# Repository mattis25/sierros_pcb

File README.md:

# sierros_pcb
Circuit of Sierros Project (self-service device which does a resuscitation) OPEN HARDWARE

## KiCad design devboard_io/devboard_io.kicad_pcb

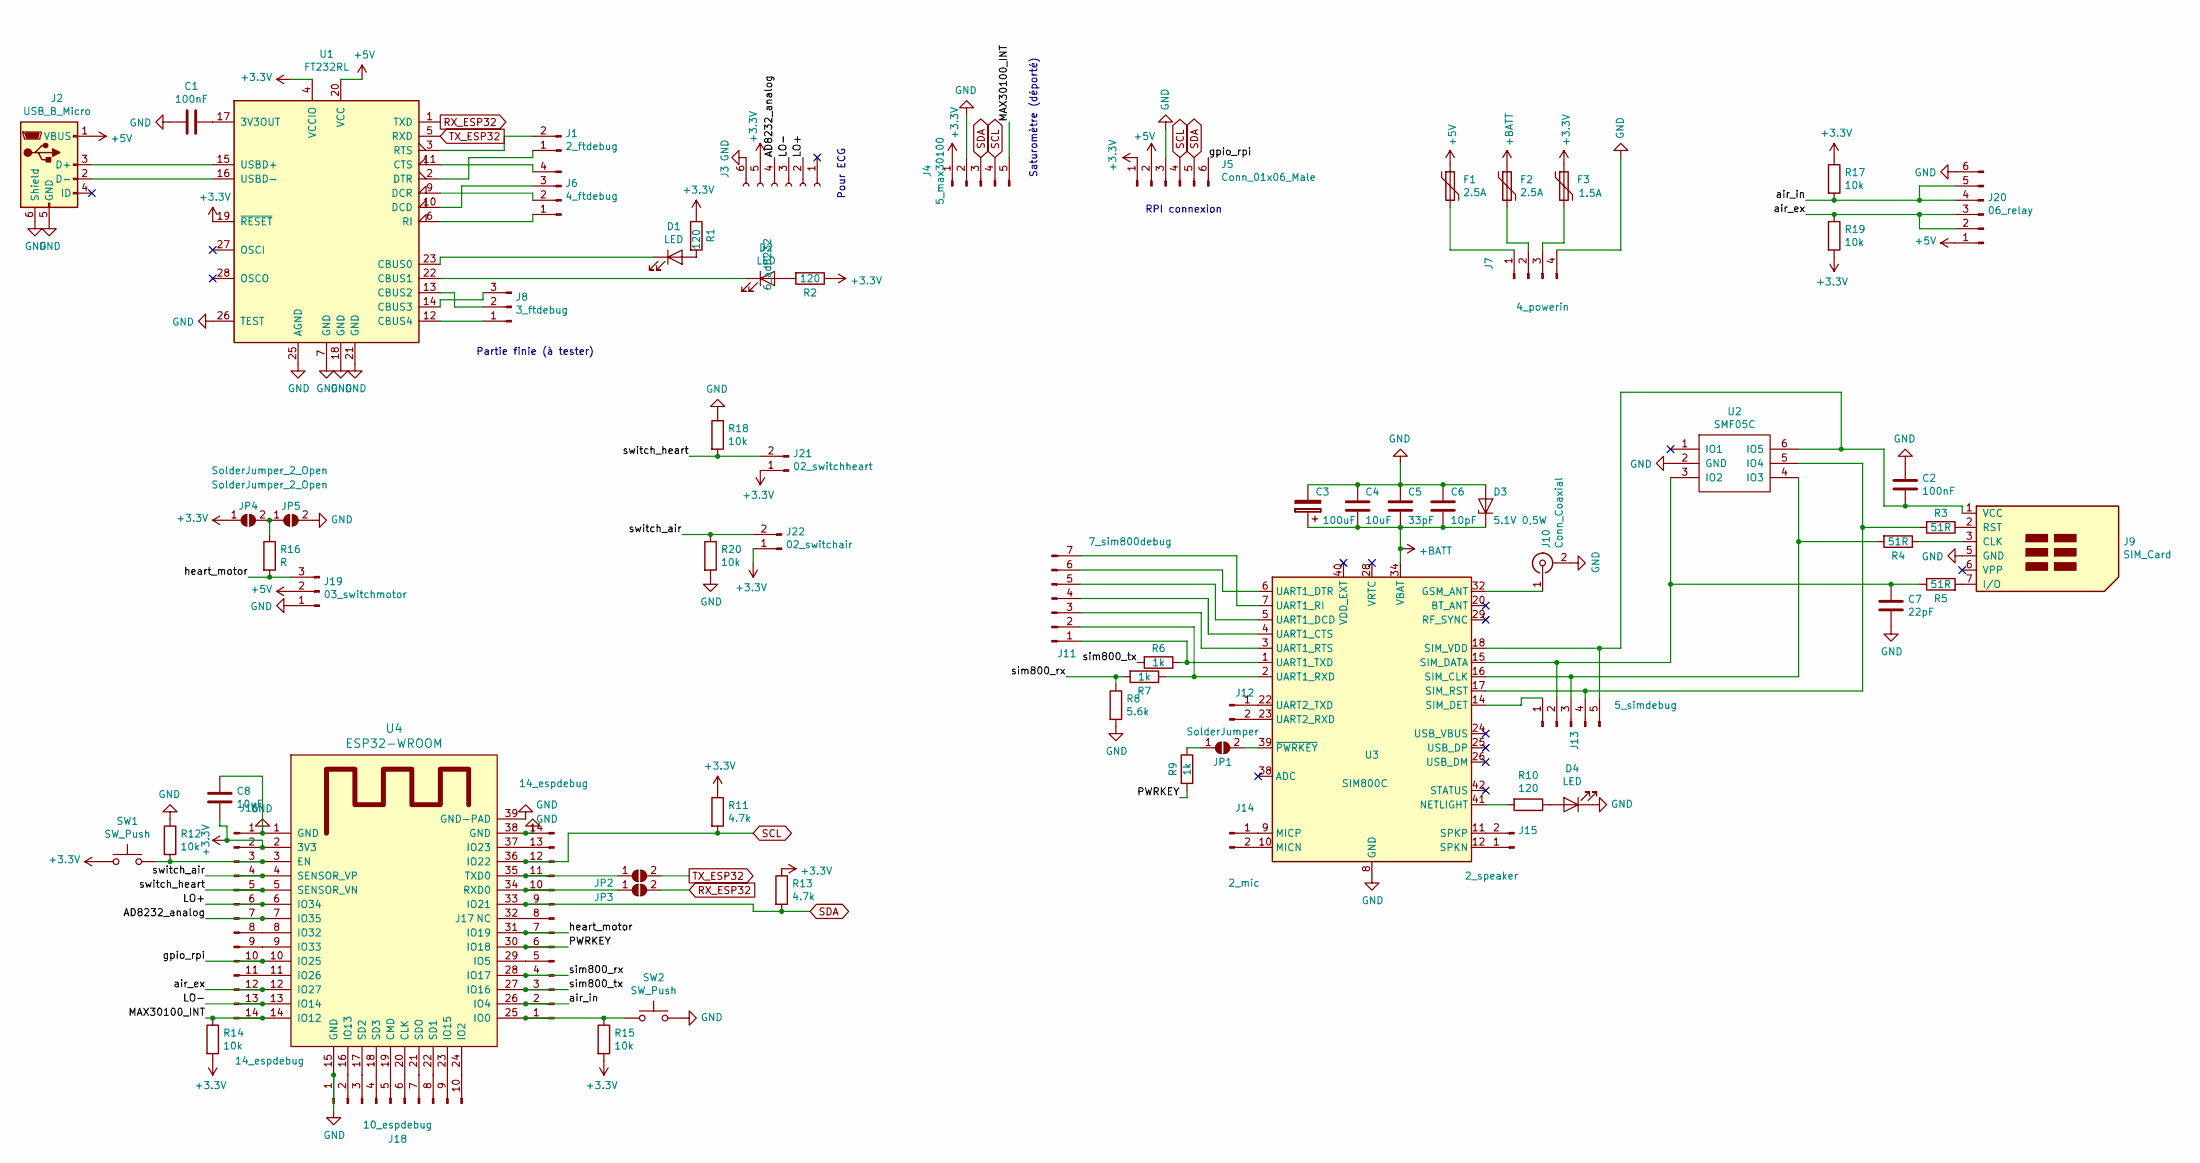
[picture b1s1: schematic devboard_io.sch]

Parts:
C1, C2: 100nF; C_1206_HandSoldering
C3: 100uF; CP_Tantalum_Case-D_EIA-7343-31_Hand
C4, C8: 10uF; C_1210_HandSoldering
C5: 33pF; C_0603_HandSoldering
C6: 10pF; C_0805_HandSoldering
C7: 22pF; C_1206_HandSoldering
D1, D2, D4: LED; LED_0805_HandSoldering
D3: 5.1V 0,5W; D_1206
F1, F2: 2.5A; C_1812_HandSoldering
F3: 1.5A; C_1812_HandSoldering
J1: 2_ftdebug; Pin_Header_Straight_1x02_Pitch2.54mm
J2: USB_B_Micro; USB-MICRO-B
J3: 6_ad8232; Pin_Header_Straight_1x06_Pitch2.54mm
J4: 5_max30100; JST_XH_B05B-XH-A_05x2.50mm_Straight
J5: Conn_01x06_Male; Pin_Header_Straight_1x06_Pitch2.54mm
J6: 4_ftdebug; Pin_Header_Straight_1x04_Pitch2.54mm
J7: 4_powerin; Pin_Header_Straight_1x04_Pitch2.54mm
J8: 3_ftdebug; Pin_Header_Straight_1x03_Pitch2.54mm
J9: SIM_Card; sim_5051
J10: Conn_Coaxial; SMA_THT_Jack_Straight
J11: 7_sim800debug; Pin_Header_Straight_1x07_Pitch2.54mm
J12: Conn_01x02_Male; Pin_Header_Straight_1x02_Pitch2.54mm
J13: 5_simdebug; Pin_Header_Straight_1x05_Pitch2.54mm
J14: 2_mic; Pin_Header_Straight_1x02_Pitch2.54mm
J15: 2_speaker; Pin_Header_Straight_1x02_Pitch2.54mm
J16, J17: 14_espdebug; Pin_Header_Straight_1x14_Pitch2.54mm
J18: 10_espdebug; Pin_Header_Straight_1x10_Pitch2.54mm
J19: 03_switchmotor; Pin_Header_Straight_1x03_Pitch2.54mm
J20: 06_relay; Pin_Header_Straight_1x06_Pitch2.54mm
J21: 02_switchheart; JST_XH_B02B-XH-A_02x2.50mm_Straight
J22: 02_switchair; JST_XH_B02B-XH-A_02x2.50mm_Straight
JP1: SolderJumper; SolderJumper-2_P1.3mm_Open_TrianglePad1.0x1.5mm
JP2, JP3, JP4, JP5: SolderJumper_2_Open; SolderJumper-2_P1.3mm_Open_TrianglePad1.0x1.5mm
R1, R2, R10: 120; R_1206_HandSoldering
R3, R4, R5: 51R; R_1206_HandSoldering
R6, R7, R9: 1k; R_1206_HandSoldering
R8: 5.6k; R_1206_HandSoldering
R11, R13: 4.7k; R_1206_HandSoldering
R12, R14, R15, R17, R18, R19, R20: 10k; R_1206_HandSoldering
R16: R; R_1206_HandSoldering
SW1, SW2: SW_Push; smd_4x4_push
U1: FT232RL; SSOP-28_5.3x10.2mm_Pitch0.65mm
U2: SMF05C; SC-70-6
U3: SIM800C
U4: ESP32-WROOM

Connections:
+3V3: C8.2, F3.1, J3.5, J4.1, J5.1, J16.2, J21.1, J22.1, JP4.1 (A), R1.1, R2.1, R11.1, R13.1, R14.2, R15.2, R17.1, R19.2, SW1.1, U1.4 (VCCIO), U1.19 (~RESET~), U4.2 (3V3)
+5V: F1.1, J2.1 (VBUS), J5.2, J19.2, J20.1, U1.20 (VCC)
+BATT: C3.1, C4.2, C5.2, C6.2, D3.1 (K), F2.1, U3.34 (VBAT), U3.35 (VBAT)
/AD8232_analog: J3.4, J16.7, U4.7 (IO35)
/LO+: J3.2, J16.6, U4.6 (IO34)
/LO-: J3.3, J16.13, U4.13 (IO14)
/MAX30100_INT: J4.5, J16.14, R14.1, U4.14 (IO12)
/PWRKEY: J17.6, R9.2, U4.30 (IO18)
/air_ex: J16.12, J20.2, J20.3, R19.1, U4.12 (IO27)
/air_in: J17.2, J20.4, J20.5, R17.2, U4.26 (IO4)
/gpio_rpi: J5.6, J16.10, U4.10 (IO25)
/heart_motor: J17.7, J19.3, R16.2, U4.31 (IO19)
/sim800_rx: J17.4, R7.2, R8.1, U4.28 (IO17)
/sim800_tx: J17.3, R6.2, U4.27 (IO16)
/switch_air: J16.4, J22.2, R20.1, U4.4 (SENSOR_VP)
/switch_heart: J16.5, J21.2, R18.2, U4.5 (SENSOR_VN)
GND: C1.2, C2.1, C3.2, C4.1, C5.1, C6.1, C7.2, C8.1, D3.2 (A), D4.1 (K), J2.5 (GND), J2.6 (Shield), J3.6, J4.2, J5.3, J7.4, J9.5 (GND), J10.2 (Ext), J16.1, J17.14, J18.1, J19.1, J20.6, JP5.2 (B), R8.2, R12.1, R18.1, R20.2, SW2.2, U1.7 (GND), U1.18 (GND), U1.21 (GND), U1.25 (AGND), U1.26 (TEST), U2.2 (GND), U3.8 (GND), U3.13 (GND), U3.19 (GND), U3.21 (GND), U3.27 (GND), U3.30 (GND), U3.31 (GND), U3.33 (GND), U3.36 (GND), U3.37 (GND), U4.1 (GND), U4.15 (GND), U4.38 (GND), U4.39 (GND-PAD)
unnamed: C1.1, U1.17 (3V3OUT)
unnamed: C2.2, J9.1 (VCC), J13.5, U2.6 (IO5), U3.18 (SIM_VDD)
unnamed: C7.1, J13.2, R5.1, U2.3 (IO2), U3.15 (SIM_DATA)
unnamed: D1.1 (K), U1.23 (CBUS0)
unnamed: D1.2 (A), R1.2
unnamed: D2.1 (K), U1.22 (CBUS1)
unnamed: D2.2 (A), R2.2
unnamed: D4.2 (A), R10.1
unnamed: F1.2, J7.1
unnamed: F2.2, J7.2
unnamed: F3.2, J7.3
unnamed: J1.1, U1.2 (DTR)
unnamed: J1.2, U1.3 (RTS)
unnamed: J2.2 (D-), U1.16 (USBD-)
unnamed: J2.3 (D+), U1.15 (USBD+)
unnamed: J6.1, U1.6 (RI)
unnamed: J6.2, U1.9 (DCR)
unnamed: J6.3, U1.10 (DCD)
unnamed: J6.4, U1.11 (CTS)
unnamed: J8.1, U1.12 (CBUS4)
unnamed: J8.2, U1.13 (CBUS2)
unnamed: J8.3, U1.14 (CBUS3)
unnamed: J9.2 (RST), R3.1
unnamed: J9.3 (CLK), R4.1
unnamed: J9.7 (I/O), R5.2
unnamed: J10.1 (In), U3.32 (GSM_ANT)
unnamed: J11.1, R6.1, U3.1 (UART1_TXD)
unnamed: J11.2, R7.1, U3.2 (UART1_RXD)
unnamed: J11.3, U3.3 (UART1_RTS)
unnamed: J11.4, U3.4 (UART1_CTS)
unnamed: J11.5, U3.5 (UART1_DCD)
unnamed: J11.6, U3.6 (UART1_DTR)
unnamed: J11.7, U3.7 (UART1_RI)
unnamed: J12.1, U3.22 (UART2_TXD)
unnamed: J12.2, U3.23 (UART2_RXD)
unnamed: J13.1, U3.14 (SIM_DET)
unnamed: J13.3, R4.2, U2.4 (IO3), U3.16 (SIM_CLK)
unnamed: J13.4, R3.2, U2.5 (IO4), U3.17 (SIM_RST)
unnamed: J14.1, U3.9 (MICP)
unnamed: J14.2, U3.10 (MICN)
unnamed: J15.1, U3.12 (SPKN)
unnamed: J15.2, U3.11 (SPKP)
unnamed: J16.3, R12.2, SW1.2, U4.3 (EN)
unnamed: J16.8, U4.8 (IO32)
unnamed: J16.9, U4.9 (IO33)
unnamed: J16.11, U4.11 (IO26)
unnamed: J17.1, R15.1, SW2.1, U4.25 (IO0)
unnamed: J17.5, U4.29 (IO5)
unnamed: J17.8, U4.32 (NC)
unnamed: J17.10, JP3.1 (A), U4.34 (RXD0)
unnamed: J17.11, JP2.1 (A), U4.35 (TXD0)
unnamed: J17.13, U4.37 (IO23)
unnamed: J18.2, U4.16 (IO13)
unnamed: J18.3, U4.17 (SD2)
unnamed: J18.4, U4.18 (SD3)
unnamed: J18.5, U4.19 (CMD)
unnamed: J18.6, U4.20 (CLK)
unnamed: J18.7, U4.21 (SDO)
unnamed: J18.8, U4.22 (SD1)
unnamed: J18.9, U4.23 (IO15)
unnamed: J18.10, U4.24 (IO2)
unnamed: JP1.1 (A), R9.1
unnamed: JP1.2 (B), U3.39 (~PWRKEY)
unnamed: JP4.2 (B), JP5.1 (A), R16.1
unnamed: R10.2, U3.41 (NETLIGHT)
RX_ESP32: JP3.2 (B), U1.1 (TXD)
SCL: J4.4, J5.4, J17.12, R11.2, U4.36 (IO22)
SDA: J4.3, J5.5, J17.9, R13.2, U4.33 (IO21)
TX_ESP32: JP2.2 (B), U1.5 (RXD)

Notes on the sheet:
Partie finie (à tester)
Pour ECG
Saturomètre (déporté)
RPI connexion

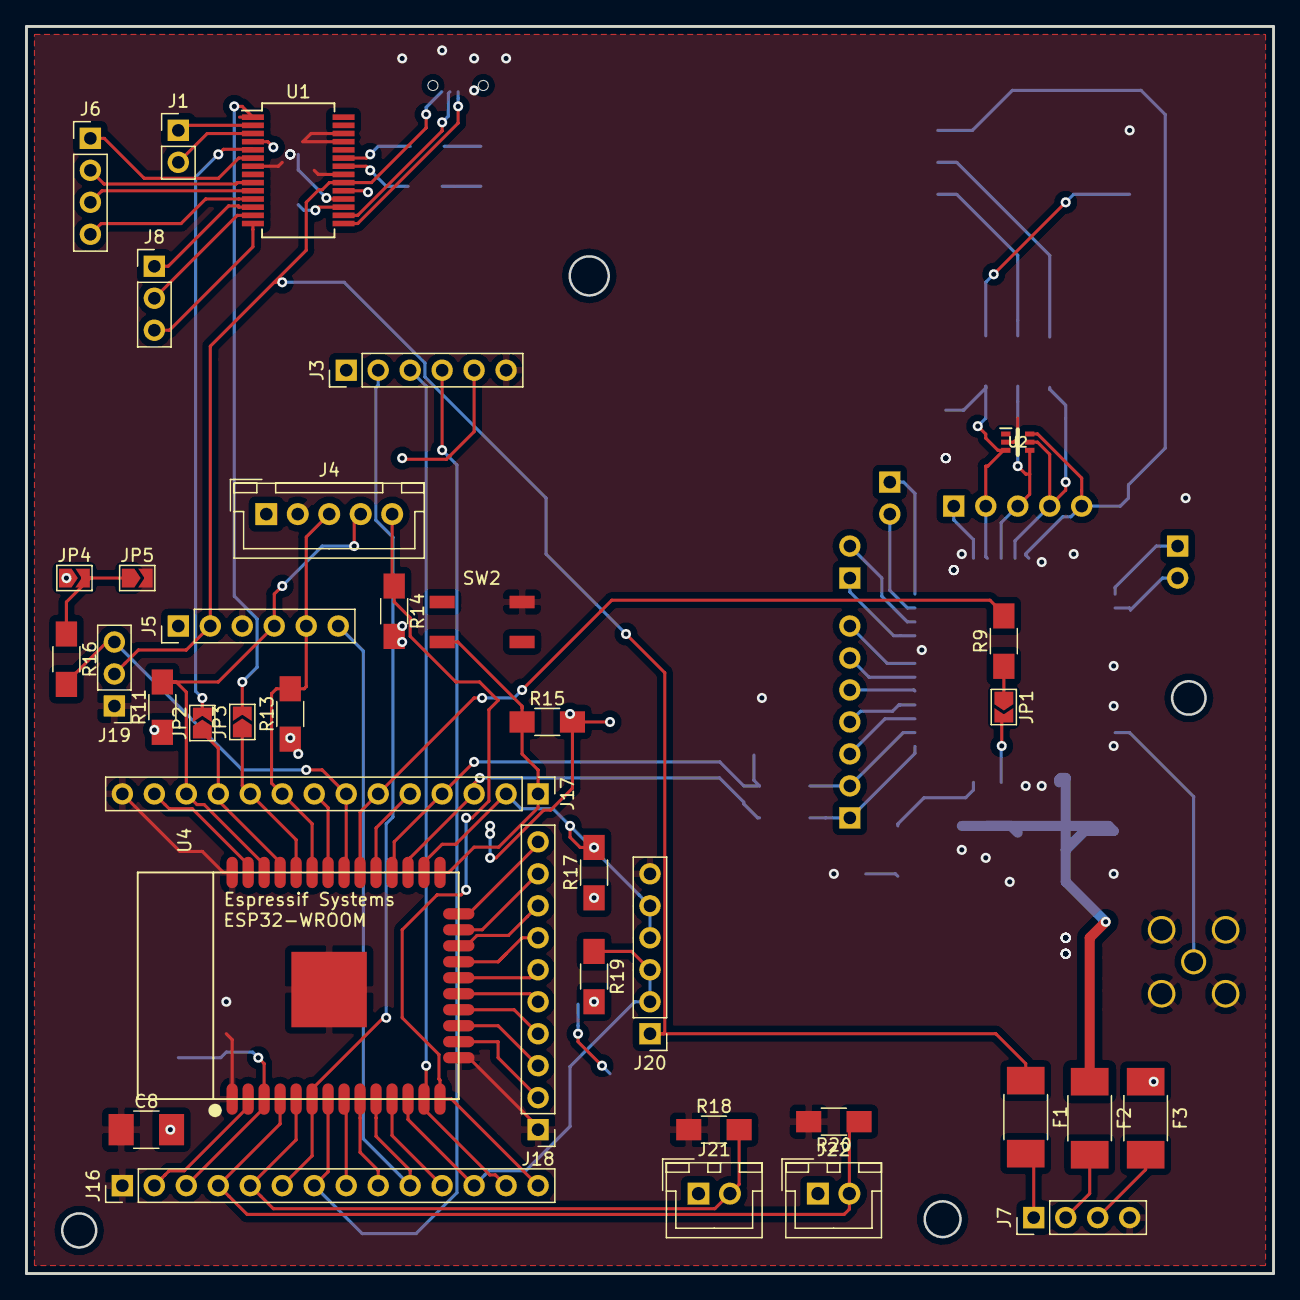
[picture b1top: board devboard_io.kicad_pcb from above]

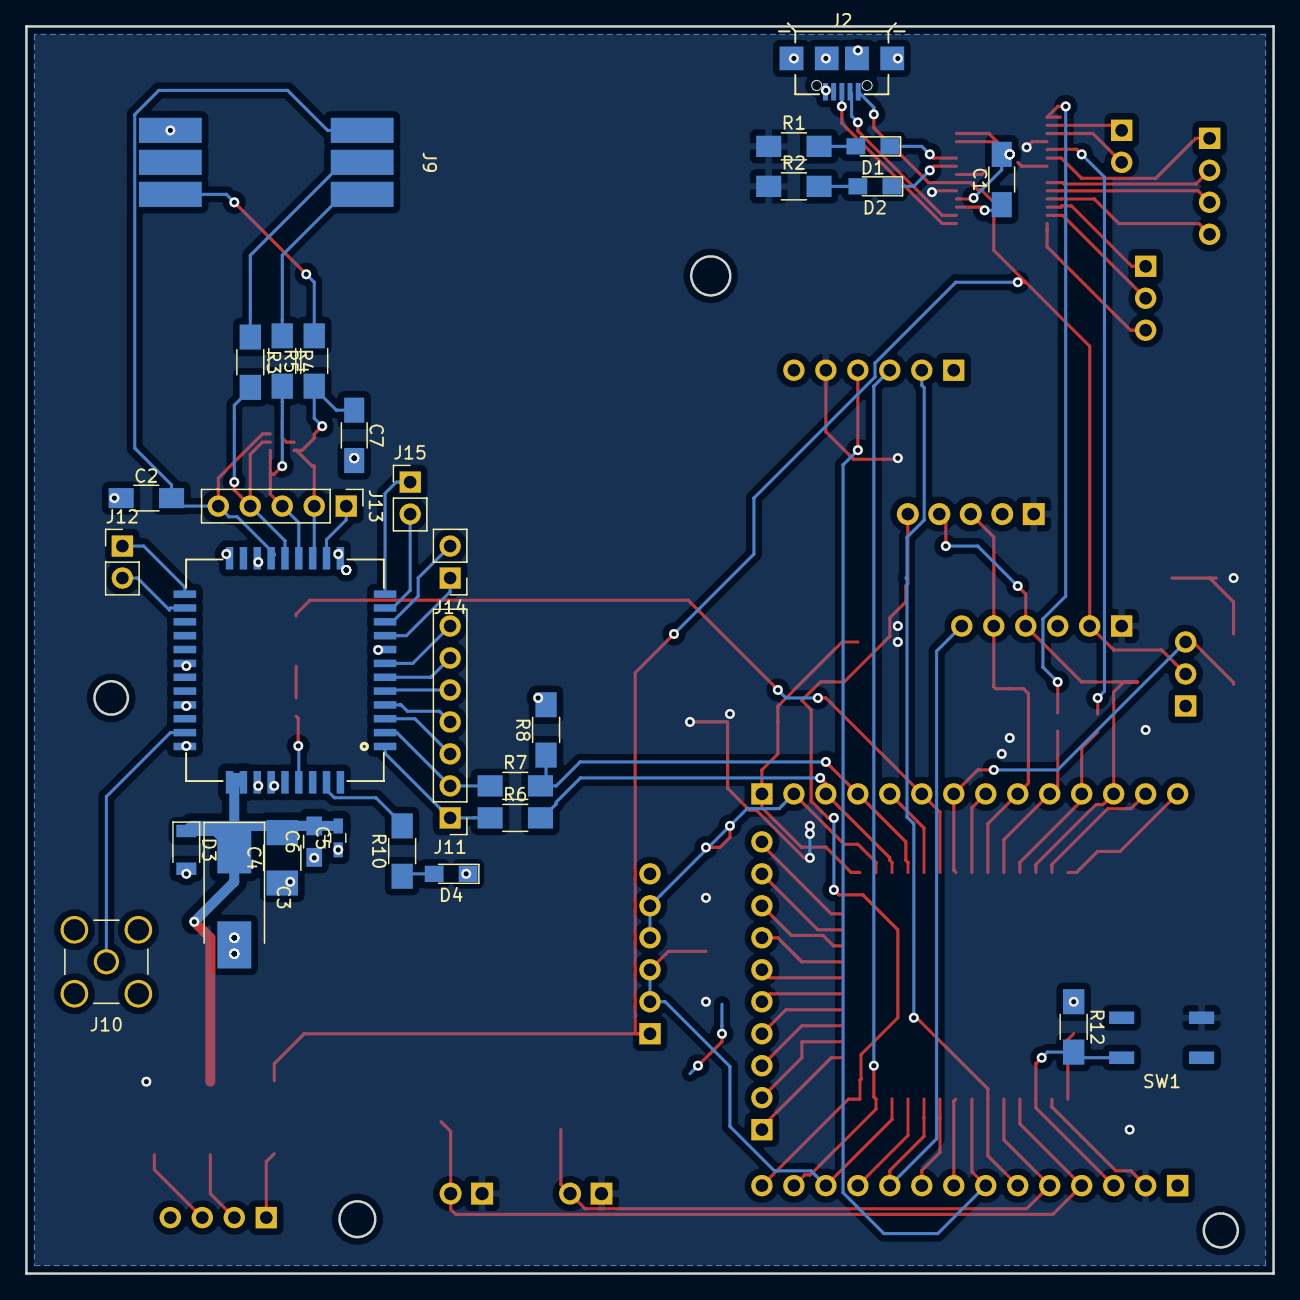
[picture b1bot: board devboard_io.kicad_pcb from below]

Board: 2 copper layers, 99.1 x 99.1 mm, 68 parts (31 on the bottom side), 86 nets.

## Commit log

2019-04-16 Upload
